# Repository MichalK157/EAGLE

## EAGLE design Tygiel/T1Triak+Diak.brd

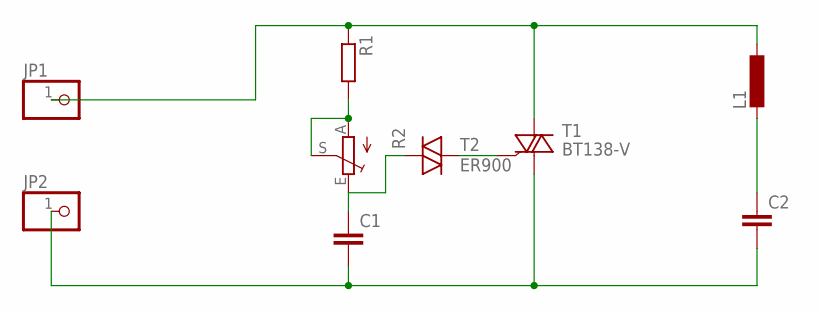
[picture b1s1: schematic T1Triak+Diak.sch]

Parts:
C1: C-EU225-062X268; C225-062X268
C2: C-EU050-030X075; C050-030X075
JP1, JP2: PINHD-1X1; 1X01
L1: L-EU0204/5; 0204/5
R1: R-EU_0207/10; 0207/10
R2: TRIM_EU-B64Y; B64Y
T1: BT138-V; TO220BV
T2: ER900

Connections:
unnamed: JP1.1, L1.1, R1.1, T1.T2 (A2)
unnamed: T1.G, T2.2
unnamed: C2.1, L1.2
unnamed: C1.2, C2.2, JP2.1, T1.T1 (A1)
unnamed: R1.2, R2.A, R2.S
unnamed: C1.1, R2.E, T2.1

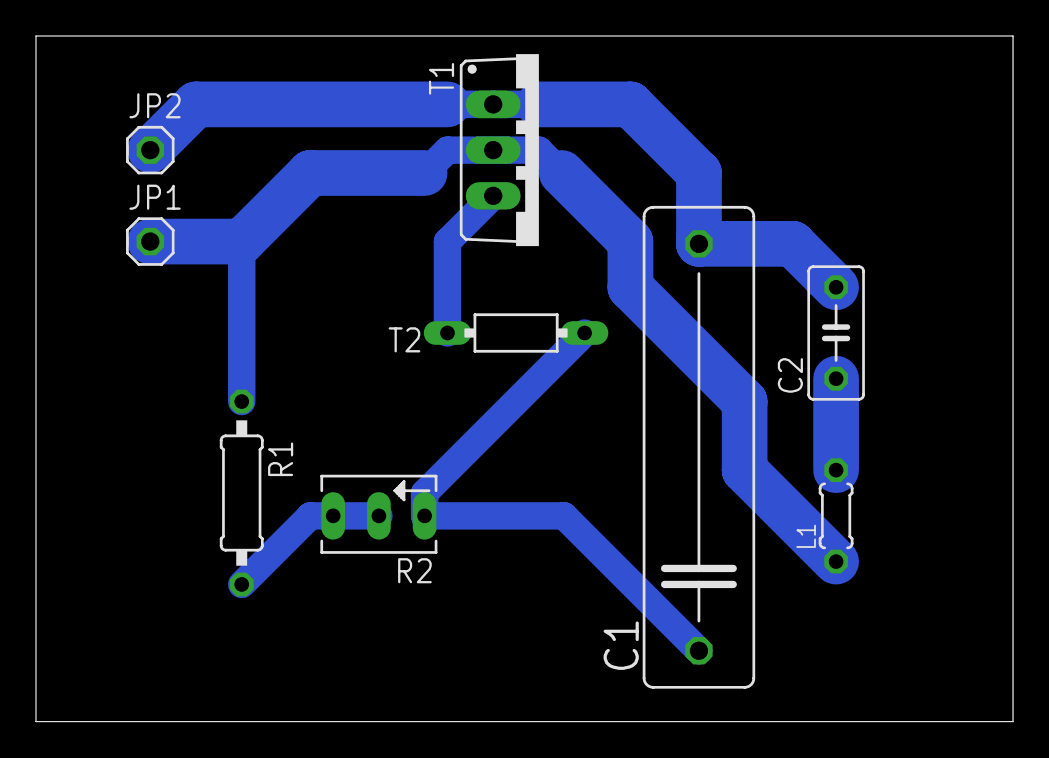
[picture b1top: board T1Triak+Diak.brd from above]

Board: 2 copper layers, 54.3 x 38.1 mm, 9 parts (0 on the bottom side), 6 nets.

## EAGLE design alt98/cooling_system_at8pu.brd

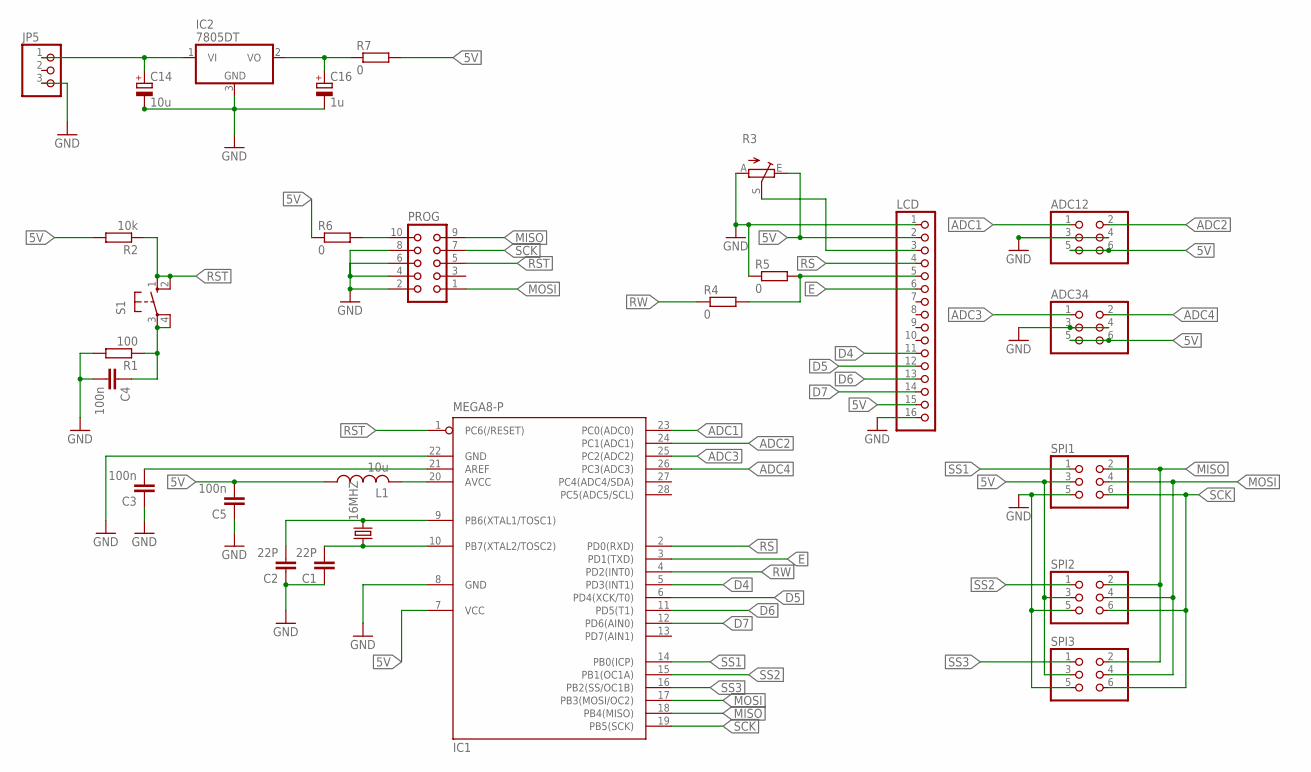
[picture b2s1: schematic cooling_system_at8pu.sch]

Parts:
16MHZ: CRYSTALHC18U-V; HC18U-V
ADC12, ADC34: PINHD-2X3; 2X03
C1, C2: 22P; C0805
C3, C4, C5: 100n; C0805
C14: 10u; 153CLV-0605
C16: 1u; 153CLV-0405
IC1: MEGA8-P; DIL28-3
IC2: 7805DT; TO252
JP5: PINHD-1X3; 1X03
L1: 10u; 0204/7
LCD: PINHD-1X16; 1X16
PROG: CON10
R1: 100; 0207/10
R2: 10k; 0207/10
R3: TRIM_EU-CT6; CT6
R4, R5, R6, R7: 0; R0805
S1: 10-XX; B3F-10XX
SPI1, SPI2, SPI3: PINHD-2X3; 2X03

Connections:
5V: ADC12.5, ADC12.6, ADC34.5, ADC34.6, C5.2, IC1.7 (VCC), L1.1, LCD.2, LCD.15, R2.2, R3.E, R6.1, R7.2, SPI1.3, SPI2.3, SPI3.3
ADC1: ADC12.1, IC1.23 (PC0(ADC0))
ADC2: ADC12.2, IC1.24 (PC1(ADC1))
ADC3: ADC34.1, IC1.25 (PC2(ADC2))
ADC4: ADC34.2, IC1.26 (PC3(ADC3))
D4: IC1.5 (PD3(INT1)), LCD.11
D5: IC1.6 (PD4(XCK/T0)), LCD.12
D6: IC1.11 (PD5(T1)), LCD.13
D7: IC1.12 (PD6(AIN0)), LCD.14
E: IC1.3 (PD1(TXD)), LCD.6
GND: ADC12.3, ADC12.4, ADC34.3, ADC34.4, C1.1, C2.1, C3.1, C4.2, C5.1, C14.-, C16.-, IC1.8 (GND), IC1.22 (GND), IC2.3 (GND), JP5.3, LCD.1, LCD.16, PROG.2, PROG.4, PROG.6, PROG.8, R1.2, R3.A, R5.1, SPI1.5, SPI2.5, SPI3.5
MISO: IC1.18 (PB4(MISO)), PROG.9, SPI1.2, SPI2.2, SPI3.2
MOSI: IC1.17 (PB3(MOSI/OC2)), PROG.1, SPI1.4, SPI2.4, SPI3.4
unnamed: 16MHZ.2, C2.2, IC1.9 (PB6(XTAL1/TOSC1))
unnamed: 16MHZ.1, C1.2, IC1.10 (PB7(XTAL2/TOSC2))
unnamed: IC1.20 (AVCC), L1.2
unnamed: C3.2, IC1.21 (AREF)
unnamed: C4.1, R1.1, S1.3, S1.4 (P1)
unnamed: LCD.5, R4.2, R5.2
unnamed: LCD.3, R3.S
unnamed: PROG.10, R6.2
unnamed: C16.+, IC2.2 (VO), R7.1
unnamed: C14.+, IC2.1 (VI), JP5.1
RS: IC1.2 (PD0(RXD)), LCD.4
RST: IC1.1 (PC6(/RESET)), PROG.5, R2.1, S1.1 (S), S1.2 (S1)
RW: IC1.4 (PD2(INT0)), R4.1
SCK: IC1.19 (PB5(SCK)), PROG.7, SPI1.6, SPI2.6, SPI3.6
SS1: IC1.14 (PB0(ICP)), SPI1.1
SS2: IC1.15 (PB1(OC1A)), SPI2.1
SS3: IC1.16 (PB2(SS/OC1B)), SPI3.1

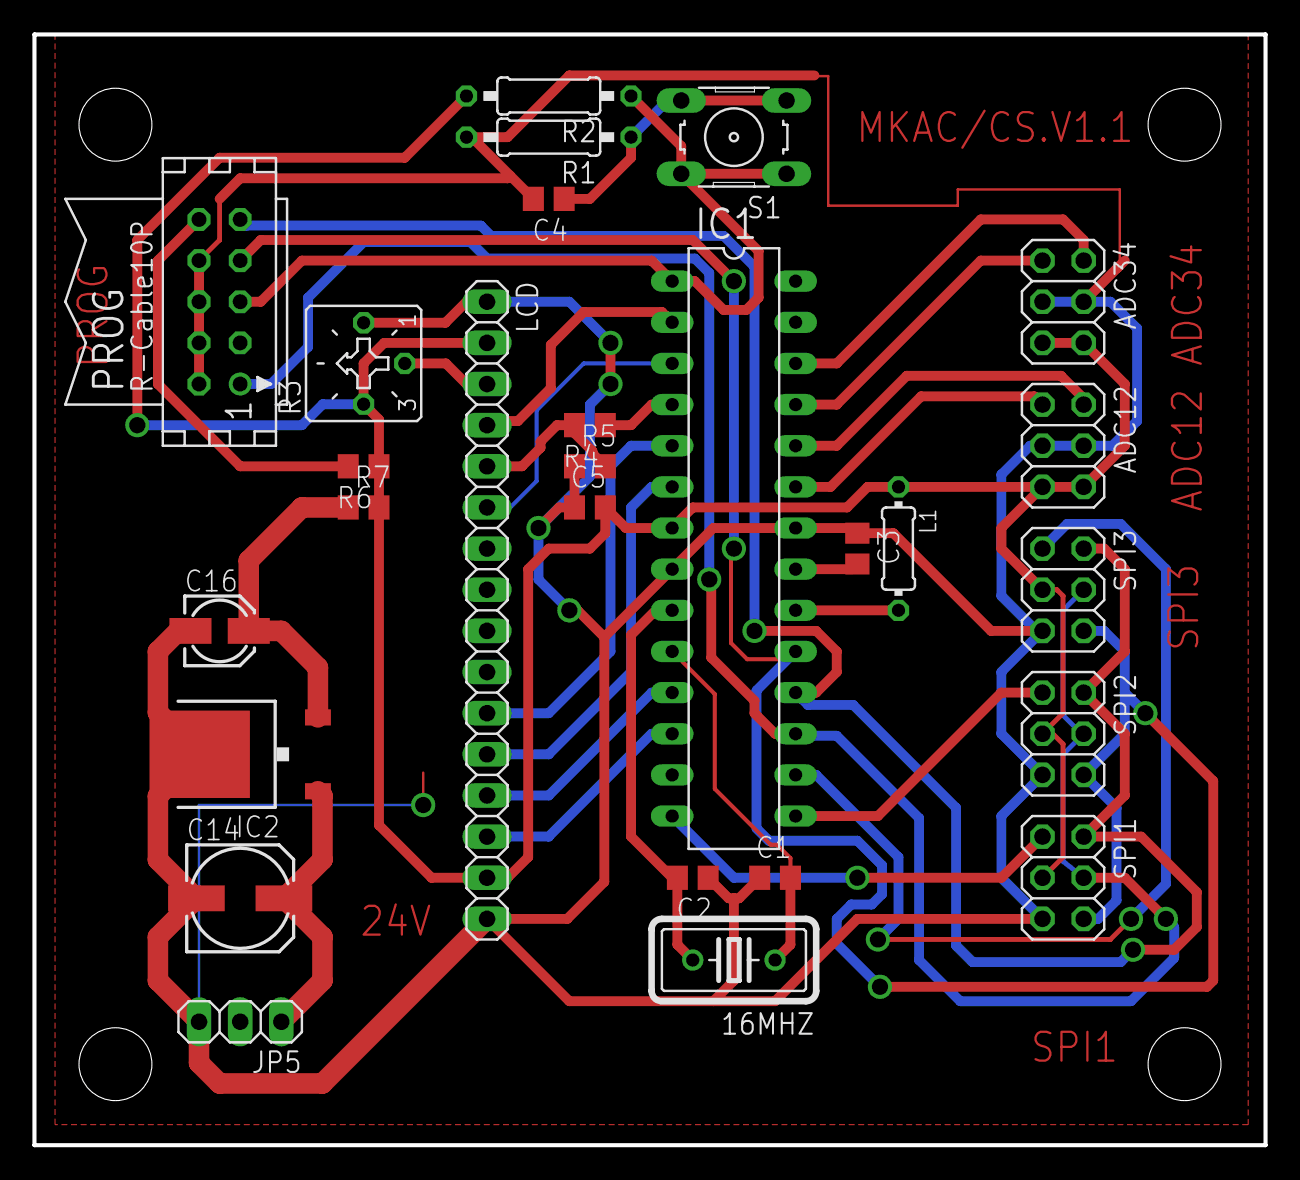
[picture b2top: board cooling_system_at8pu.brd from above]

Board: 2 copper layers, 76.0 x 68.6 mm, 27 parts (0 on the bottom side), 30 nets.

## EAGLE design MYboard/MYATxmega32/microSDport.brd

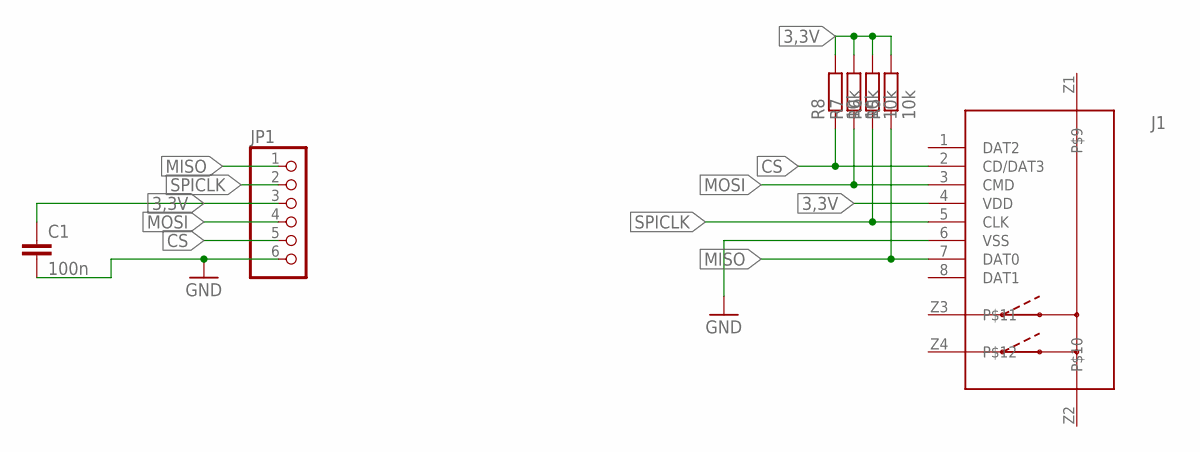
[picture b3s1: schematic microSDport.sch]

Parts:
C1: 100n; C0805K
J1: 693072010801
JP1: PINHD-1X6; 1X06
R5, R6, R7, R8: 10k; R0805

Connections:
3,3V: C1.1, J1.4 (VDD), JP1.3, R5.2, R6.2, R7.2, R8.2
CS: J1.2 (CD/DAT3), JP1.5, R8.1
GND: C1.2, J1.6 (VSS), JP1.6
MISO: J1.7 (DAT0), JP1.1, R5.1
MOSI: J1.3 (CMD), JP1.4, R7.1
SPICLK: J1.5 (CLK), JP1.2, R6.1

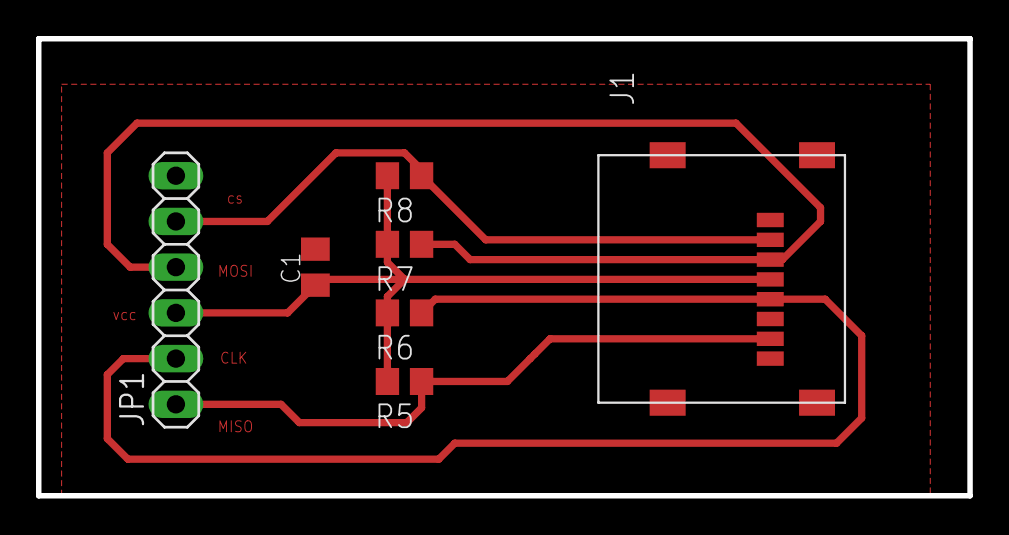
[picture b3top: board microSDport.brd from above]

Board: 2 copper layers, 51.7 x 25.4 mm, 7 parts (0 on the bottom side), 6 nets.

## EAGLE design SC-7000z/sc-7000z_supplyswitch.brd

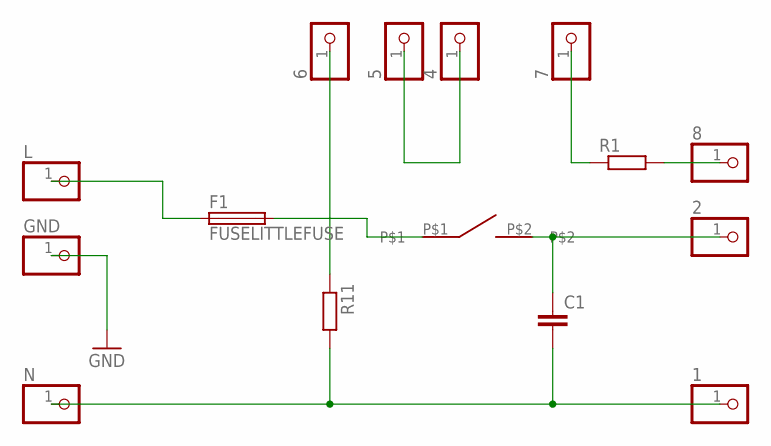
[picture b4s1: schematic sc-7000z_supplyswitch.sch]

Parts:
1, 2, 4, 5, 6, 7, 8: PINHD-1X1; 1X01
C1: C-EU150-054X183; C150-054X183
F1: FUSELITTLEFUSE; LITTLEFUSE
GND: PINHD-1X1; 1X01
L: PINHD-1X1; 1X01
N: PINHD-1X1; 1X01
R1, R11: R-EU_0309/12; 0309/12
U$1: MY_SWITCH_ON_OFF; KOLYSKA21X15

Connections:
GND: GND.1
unnamed: 7.1, R1.1
unnamed: 8.1, R1.2
unnamed: 6.1, R11.1
unnamed: 4.1, 5.1
unnamed: F1.2, U$1.P$1
unnamed: 2.1, C1.1, U$1.P$2
unnamed: 1.1, C1.2, N.1, R11.2
unnamed: F1.1, L.1

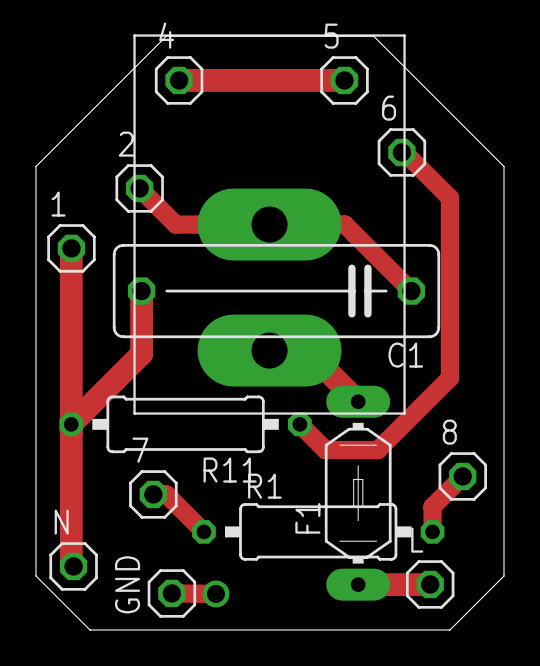
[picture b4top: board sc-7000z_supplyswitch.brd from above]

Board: 2 copper layers, 26.0 x 33.0 mm, 15 parts (0 on the bottom side), 8 nets.

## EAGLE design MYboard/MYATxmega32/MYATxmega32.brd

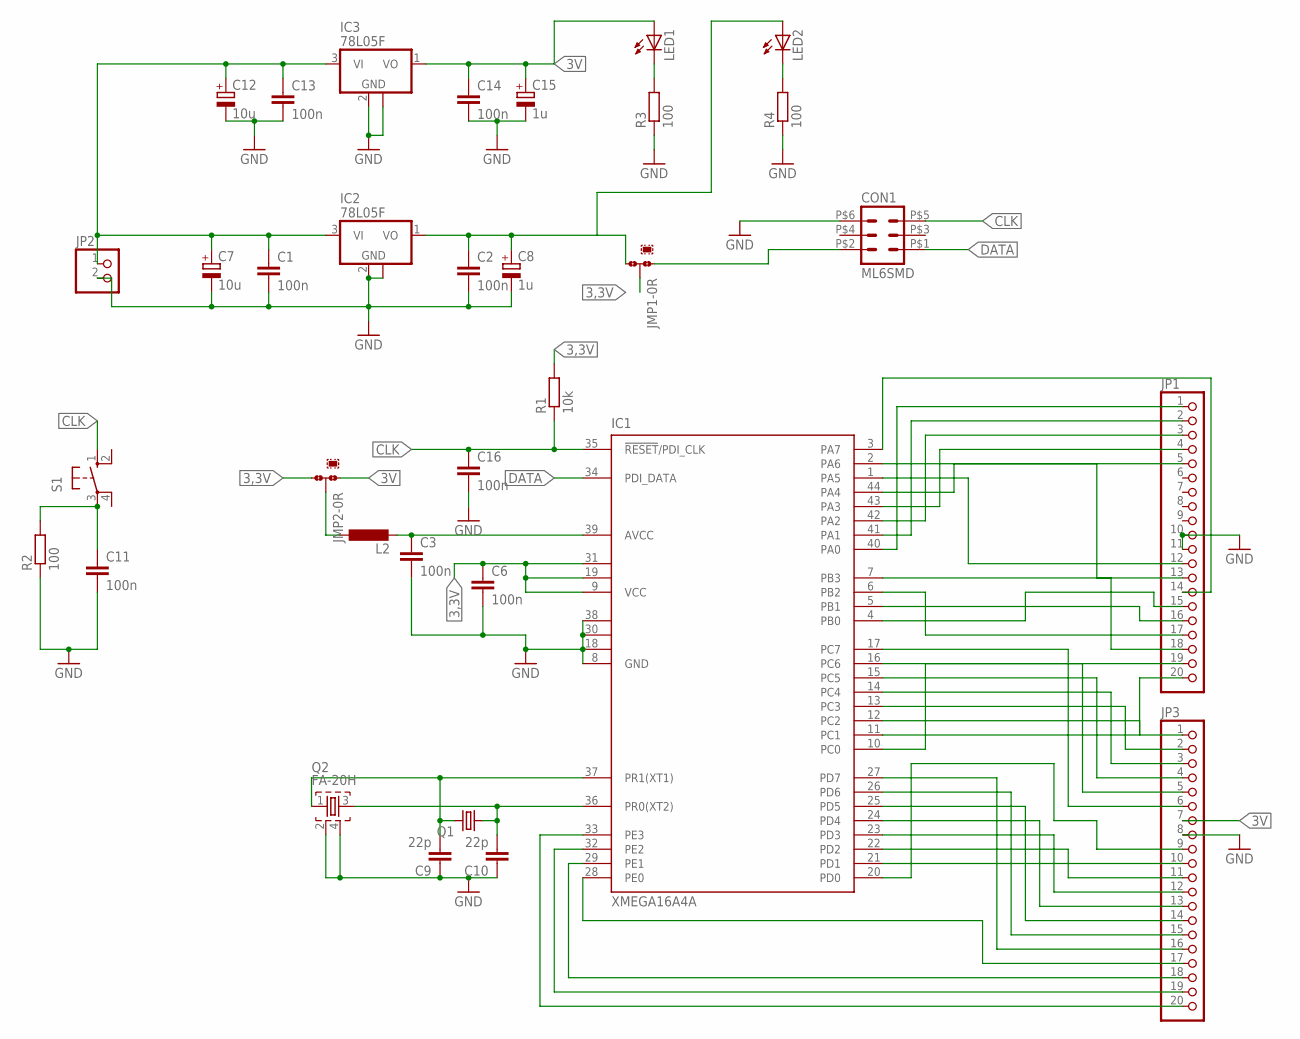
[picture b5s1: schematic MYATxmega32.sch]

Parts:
C1, C2, C3, C6, C11, C13, C14, C16: 100n; C0805K
C7, C12: 10u; E2-5
C8, C15: 1u; 153CLV-0405
C9, C10: 22p; C0805K
CON1: ML6SMD; CON06
IC1: XMEGA16A4A; TQFP44
IC2, IC3: 78L05F; SOT89
JMP1, JMP2: 0R-JUMPA; A0R-JMP
JP1, JP3: PINHD-1X20; 1X20
JP2: PINHD-1X2; 1X02
L2: L-EU0207/7; 0207/7
LED1, LED2: LEDSML0805; SML0805
Q1: CRYSTALHC18U-V; HC18U-V
Q2: FA-20H
R1: 10k; R0805
R2, R3, R4: 100; R0805
S1: 10-XX; B3F-10XX

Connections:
3,3V: C6.1, IC1.9 (VCC), IC1.19 (VCC1), IC1.31 (VCC2), JMP1.2, JMP2.3, R1.2
3V: C14.1, C15.+, IC3.1 (VO), JMP2.1, JP3.7, LED1.A
CLK: C16.1, CON1.P$5 (5), IC1.35 (!RESET!/PDI_CLK), R1.1, S1.1 (S)
DATA: CON1.P$1 (1), IC1.34 (PDI_DATA)
GND: C1.2, C2.2, C3.2, C6.2, C7.-, C8.-, C9.1, C10.1, C11.2, C12.-, C13.2, C14.2, C15.-, C16.2, CON1.P$6 (6), IC1.8 (GND), IC1.18 (GND1), IC1.30 (GND2), IC1.38 (GND3), IC2.2 (GND), IC2.2@1 (GND), IC3.2 (GND), IC3.2@1 (GND), JP1.10, JP1.11, JP2.2, JP3.8, Q2.2, Q2.4, R2.1, R3.1, R4.1
unnamed: C2.1, C8.+, IC2.1 (VO), JMP1.3, LED2.A
unnamed: C1.1, C7.+, C12.+, C13.1, IC2.3 (VI), IC3.3 (VI), JP2.1
unnamed: JMP2.2, L2.1
unnamed: C9.2, IC1.37 (PR1(XT1)), Q1.2, Q2.1
unnamed: C11.1, R2.2, S1.3
unnamed: C3.1, IC1.39 (AVCC), L2.2
unnamed: IC1.3 (PA7), JP1.14
unnamed: IC1.12 (PC2), JP3.1
unnamed: IC1.2 (PA6), JP1.13
unnamed: CON1.P$2 (2), JMP1.1
unnamed: IC1.44 (PA4), JP1.5
unnamed: IC1.43 (PA3), JP1.4
unnamed: IC1.42 (PA2), JP1.3
unnamed: IC1.41 (PA1), JP1.2
unnamed: IC1.13 (PC3), JP3.2
unnamed: IC1.4 (PB0), JP1.15
unnamed: IC1.5 (PB1), JP1.16
unnamed: IC1.6 (PB2), JP1.17
unnamed: IC1.7 (PB3), JP1.18
unnamed: IC1.40 (PA0), JP1.1
unnamed: LED1.C, R3.2
unnamed: C10.2, IC1.36 (PR0(XT2)), Q1.1, Q2.3
unnamed: IC1.14 (PC4), JP3.3
unnamed: IC1.15 (PC5), JP3.4
unnamed: IC1.16 (PC6), JP3.5
unnamed: IC1.17 (PC7), JP3.6
unnamed: IC1.1 (PA5), JP1.12
unnamed: LED2.C, R4.2
unnamed: IC1.21 (PD1), JP3.10
unnamed: IC1.20 (PD0), JP3.9
unnamed: IC1.22 (PD2), JP3.11
unnamed: IC1.23 (PD3), JP3.12
unnamed: IC1.24 (PD4), JP3.13
unnamed: IC1.25 (PD5), JP3.14
unnamed: IC1.26 (PD6), JP3.15
unnamed: IC1.27 (PD7), JP3.16
unnamed: IC1.28 (PE0), JP3.17
unnamed: IC1.29 (PE1), JP3.18
unnamed: IC1.32 (PE2), JP3.19
unnamed: IC1.33 (PE3), JP3.20
unnamed: IC1.10 (PC0), JP1.19
unnamed: IC1.11 (PC1), JP1.20

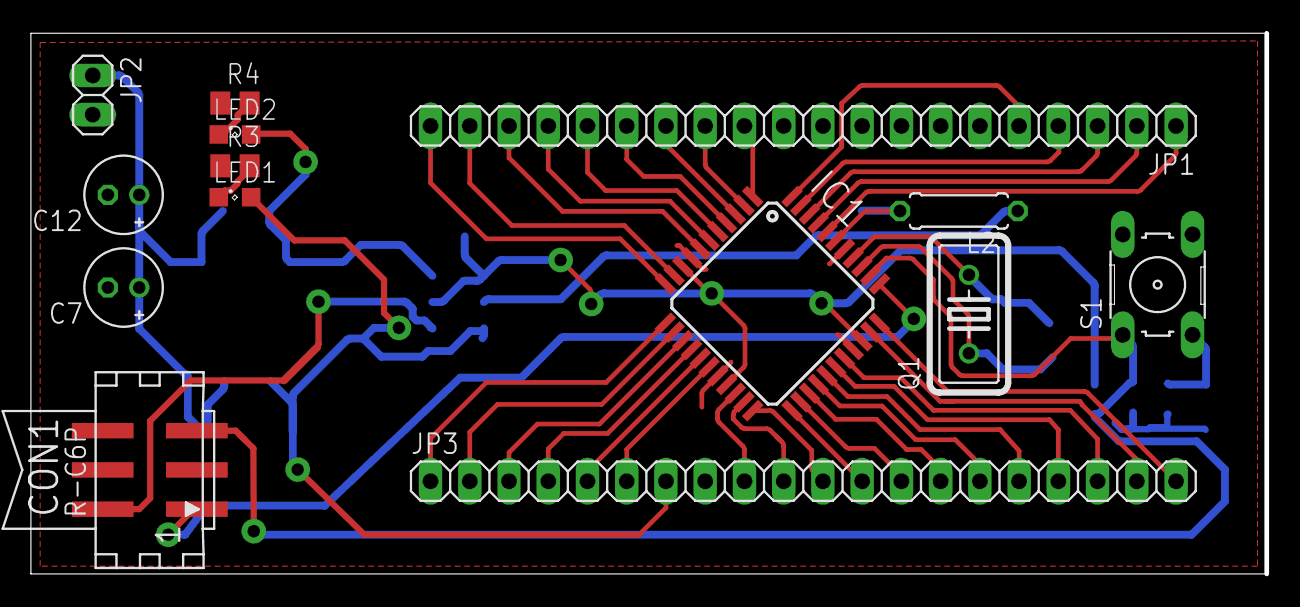
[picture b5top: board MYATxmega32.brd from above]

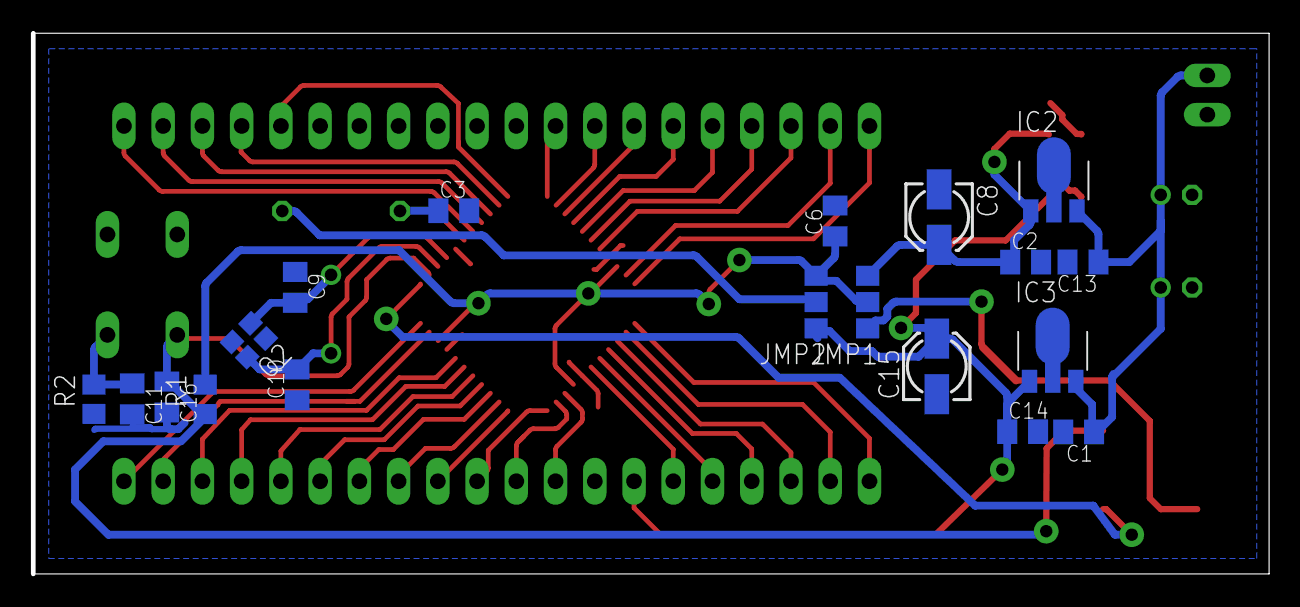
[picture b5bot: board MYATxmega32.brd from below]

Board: 2 copper layers, 80.0 x 35.0 mm, 33 parts (19 on the bottom side), 47 nets.

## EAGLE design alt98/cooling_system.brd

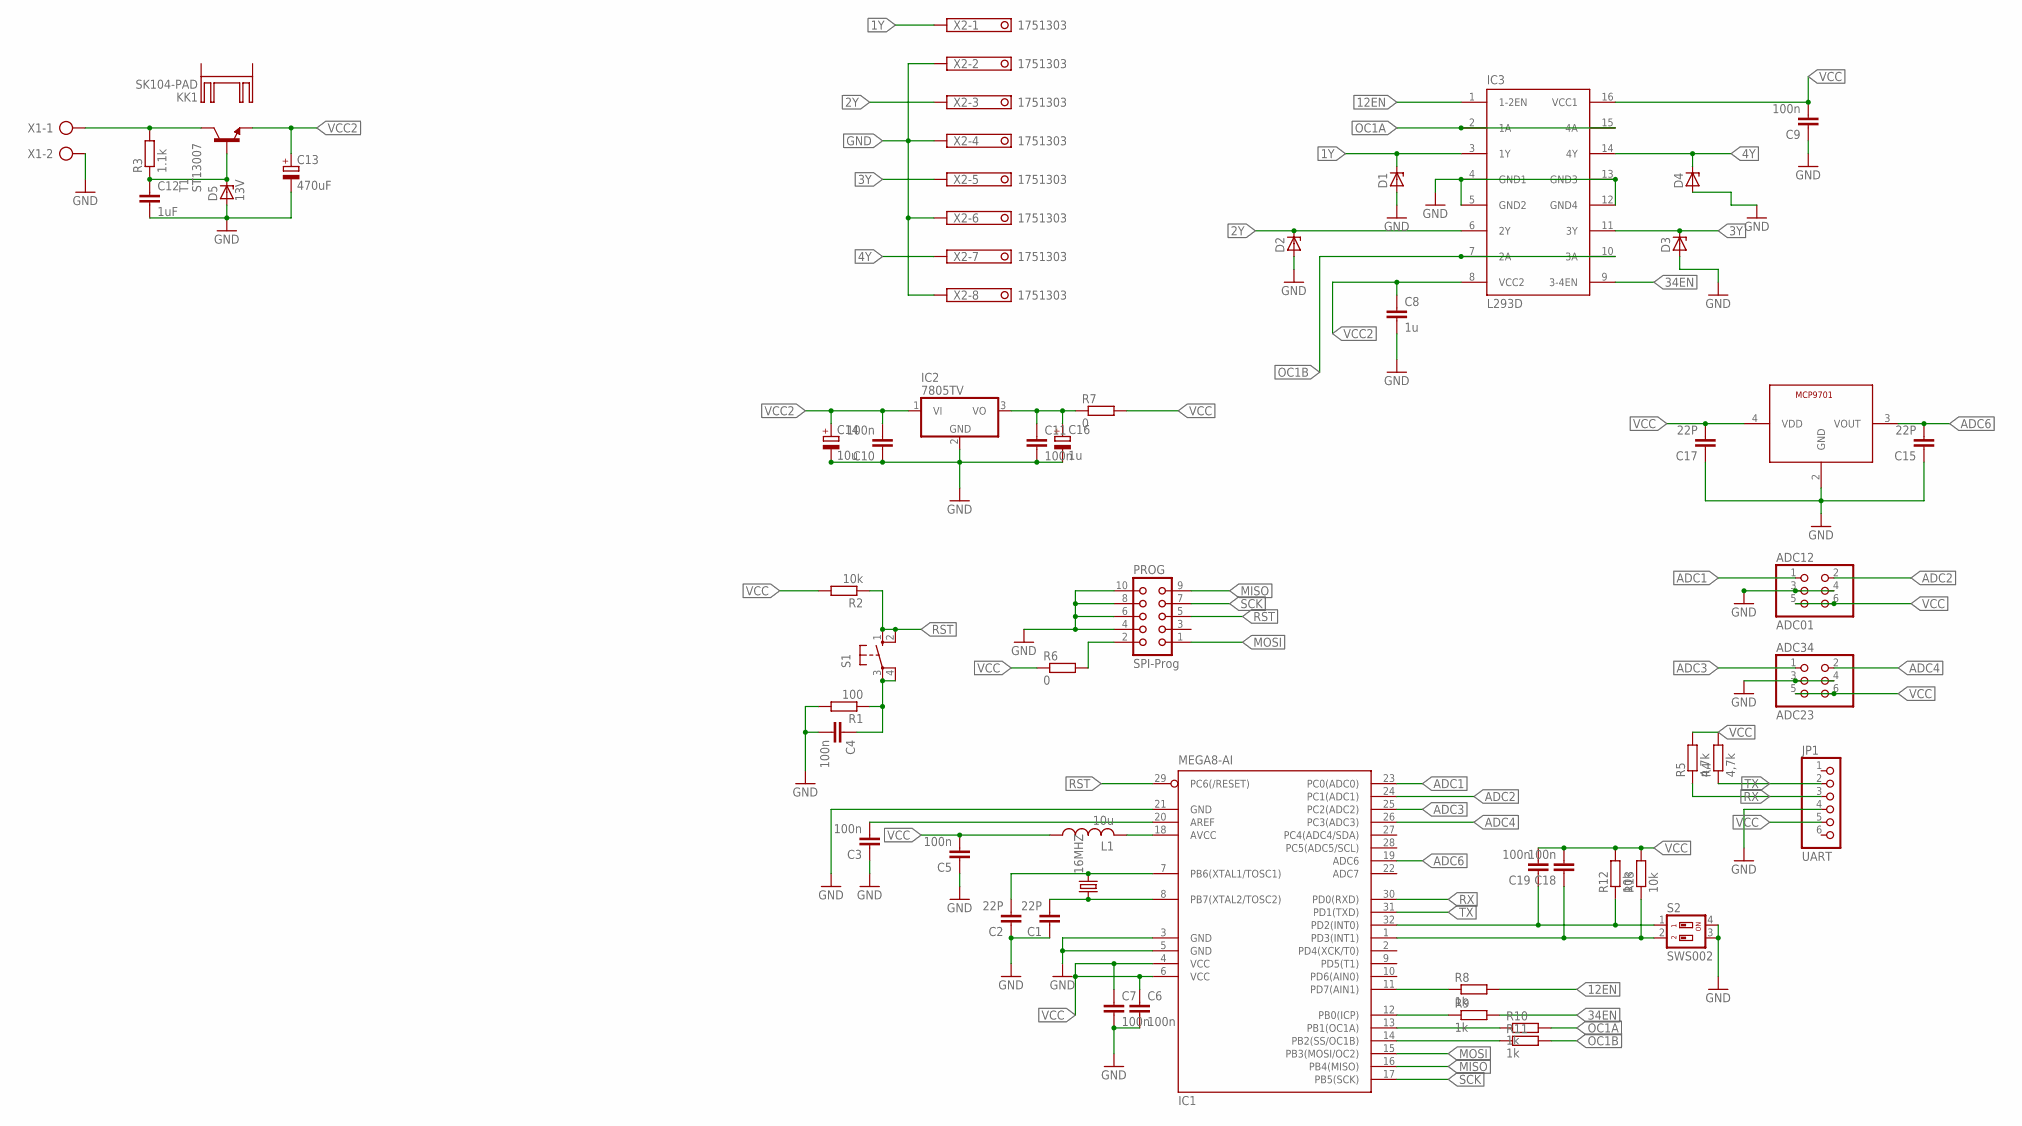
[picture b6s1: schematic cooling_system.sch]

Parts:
16MHZ: CRYSTALHC18U-V; HC18U-V
ADC12: ADC01; 2X03
ADC34: ADC23; 2X03
C1, C2, C15, C17: 22P; C0805K
C3, C4, C5, C6, C7, C9, C10, C11, C18, C19: 100n; C0805K
C8: 1u; C0805K
C12: 1uF; C0805K
C13: 470uF; E5-10,5
C14: 10u; 153CLV-0505
C16: 1u; 153CLV-0405
D1, D2, D3, D4: ZENER-DIODEDO35Z10; DO35Z10
D5: 13V; SOT23
IC1: MEGA8-AI; TQFP32-08
IC2: 7805TV; TO220V
IC3: L293D; DIL16
JP1: UART; 1X06
KK1: SK104-PAD
L1: 10u; 0207/10
PROG: SPI-Prog; CON10
R1: 100; 0207/10
R2: 10k; 0207/10
R3: 1.1k; R0805
R4, R5: 4,7k; R0805
R6, R7: 0; R0805
R8, R9, R10, R11: 1k; R0805
R12, R13: 10k; R0805
S1: 10-XX; B3F-10XX
S2: SWS002; SMS-002
T1: ST13007; TO220AV
U$2: MCP9701; SC70-5L
X1: AK300/2
X2: 1751303

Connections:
1Y: D1.C, IC3.3 (1Y), X2.1
2Y: D2.C, IC3.6 (2Y), X2.3
3Y: D3.C, IC3.11 (3Y), X2.5
4Y: D4.C, IC3.14 (4Y), X2.7
12EN: IC3.1 (1-2EN), R8.2
34EN: IC3.9 (3-4EN), R9.2
ADC1: ADC12.1, IC1.23 (PC0(ADC0))
ADC2: ADC12.2, IC1.24 (PC1(ADC1))
ADC3: ADC34.1, IC1.25 (PC2(ADC2))
ADC4: ADC34.2, IC1.26 (PC3(ADC3))
ADC6: C15.2, IC1.19 (ADC6), U$2.3 (VOUT)
AREF: C3.2, IC1.20 (AREF)
AVCC: IC1.18 (AVCC), L1.2
GND: ADC12.3, ADC12.4, ADC34.3, ADC34.4, C1.1, C2.1, C3.1, C4.2, C5.1, C6.2, C7.2, C8.2, C9.1, C10.1, C11.2, C12.2, C13.-, C14.-, C15.1, C16.-, C17.1, D1.A, D2.A, D3.A, D4.A, D5.1 (A), IC1.3 (GND), IC1.5 (GND), IC1.21 (GND), IC2.2 (GND), IC3.4 (GND1), IC3.5 (GND2), IC3.12 (GND4), IC3.13 (GND3), JP1.4, PROG.4, PROG.6, PROG.8, PROG.10, R1.2, S2.3, S2.4, U$2.2 (GND), X1.2, X2.2, X2.4, X2.6, X2.8
MISO: IC1.16 (PB4(MISO)), PROG.9
MOSI: IC1.15 (PB3(MOSI/OC2)), PROG.1
unnamed: 16MHZ.2, C2.2, IC1.7 (PB6(XTAL1/TOSC1))
unnamed: 16MHZ.1, C1.2, IC1.8 (PB7(XTAL2/TOSC2))
unnamed: IC1.14 (PB2(SS/OC1B)), R11.1
unnamed: IC1.13 (PB1(OC1A)), R10.1
unnamed: PROG.2, R6.2
unnamed: C4.1, R1.1, S1.3, S1.4 (P1)
unnamed: R3.2, T1.2 (C), X1.1
unnamed: C12.1, D5.3 (C), R3.1, T1.1 (B)
unnamed: IC1.12 (PB0(ICP)), R9.1
unnamed: IC1.11 (PD7(AIN1)), R8.1
unnamed: C19.1, IC1.32 (PD2(INT0)), R12.1, S2.1
unnamed: C18.1, IC1.1 (PD3(INT1)), R13.1, S2.2
unnamed: C11.1, C16.+, IC2.3 (VO), R7.1
OC1A: IC3.2 (1A), IC3.15 (4A), R10.2
OC1B: IC3.7 (2A), IC3.10 (3A), R11.2
RST: IC1.29 (PC6(/RESET)), PROG.5, R2.1, S1.1 (S), S1.2 (S1)
RX: IC1.30 (PD0(RXD)), JP1.3, R5.1
SCK: IC1.17 (PB5(SCK)), PROG.7
TX: IC1.31 (PD1(TXD)), JP1.2, R4.1
VCC: ADC12.5, ADC12.6, ADC34.5, ADC34.6, C5.2, C6.1, C7.1, C9.2, C17.2, C18.2, C19.2, IC1.4 (VCC), IC1.6 (VCC), IC3.16 (VCC1), JP1.5, L1.1, R2.2, R4.2, R5.2, R6.1, R7.2, R12.2, R13.2, U$2.4 (VDD)
VCC2: C8.1, C10.2, C13.+, C14.+, IC2.1 (VI), IC3.8 (VCC2), T1.3 (E)

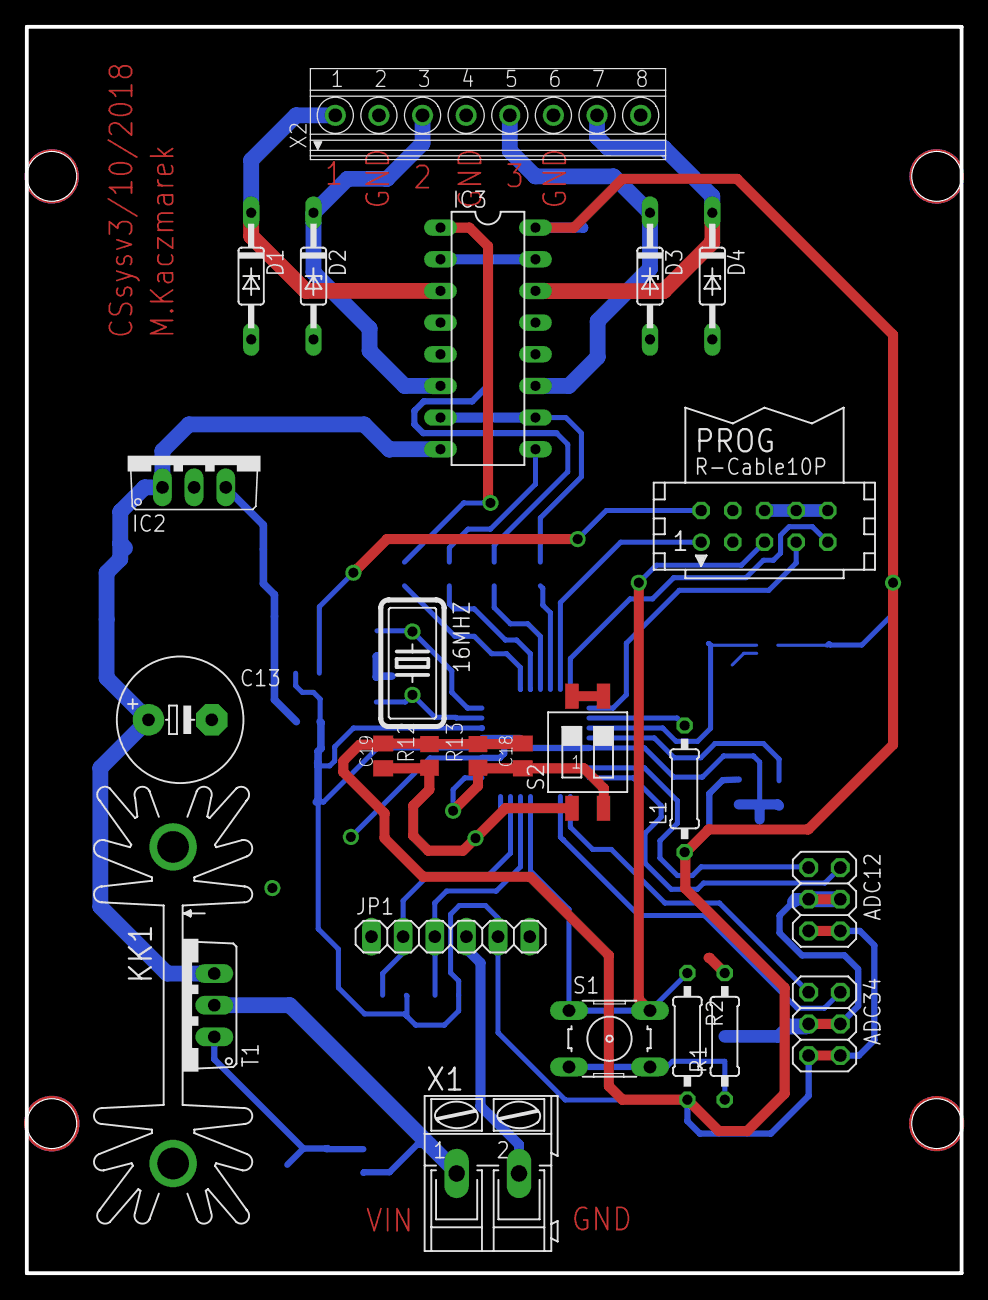
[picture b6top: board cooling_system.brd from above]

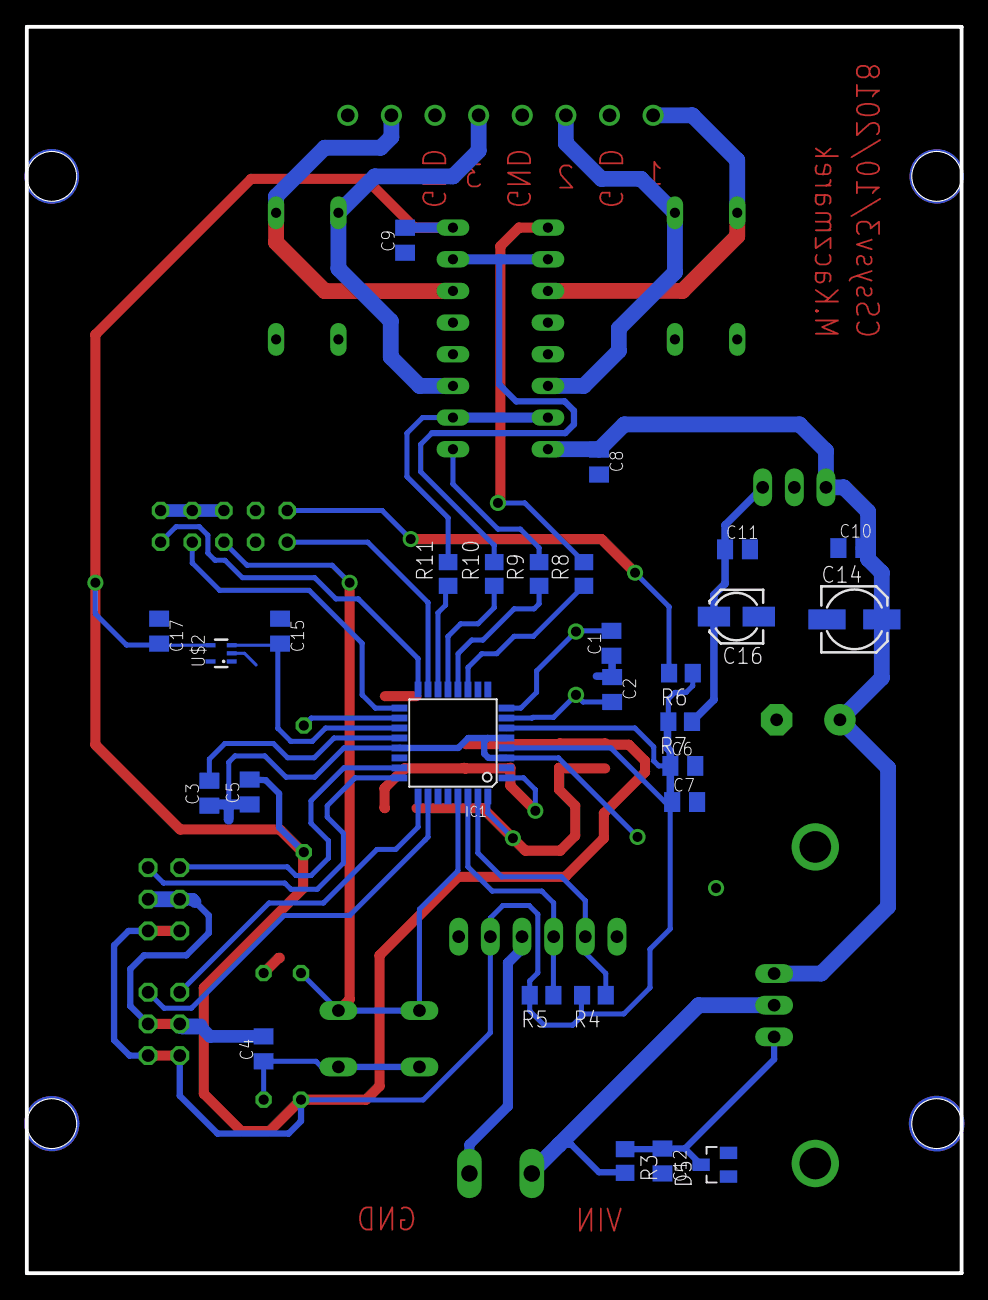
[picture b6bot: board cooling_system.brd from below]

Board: 2 copper layers, 75.0 x 100.0 mm, 53 parts (28 on the bottom side), 37 nets.

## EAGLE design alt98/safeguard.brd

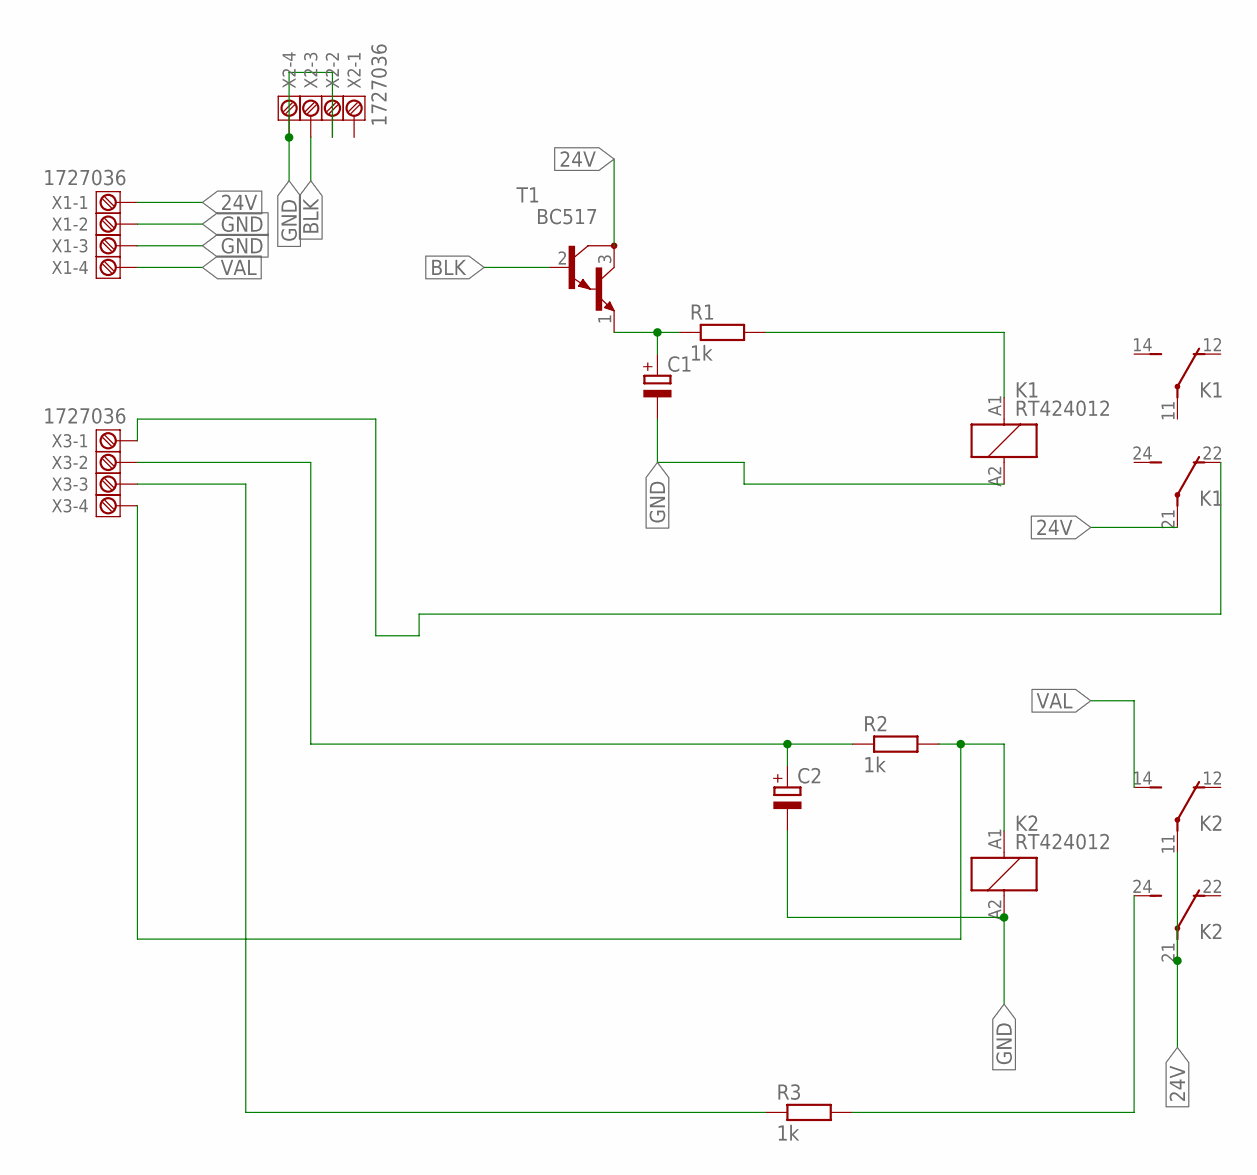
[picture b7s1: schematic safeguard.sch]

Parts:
C1, C2: CPOL-EU153CLV-0405; 153CLV-0405
K1, K2: RT424012; RT2C/O
R1, R2, R3: 1k; 0204/7
T1: BC517; TO92
X1, X2, X3: 1727036

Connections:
24V: K1.21, K2.11, K2.21, T1.3 (C), X1.1
BLK: T1.2 (B), X2.3
GND: C1.-, C2.-, K1.A2 (2), K2.A2 (2), X1.2, X1.3, X2.2, X2.4
unnamed: K1.22 (O), X3.1
unnamed: K2.A1 (1), R2.2, X3.4
unnamed: C1.+, R1.1, T1.1 (E)
unnamed: K1.A1 (1), R1.2
unnamed: C2.+, R2.1, X3.2
unnamed: K2.24 (S), R3.2
unnamed: R3.1, X3.3
VAL: K2.14 (S), X1.4

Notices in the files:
parts and their libraries:
Wurth_Elektronik_Electromechanic_Input-O: Copyright: Würth Elektronik
